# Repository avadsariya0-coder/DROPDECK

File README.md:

# DROPDECK
A Macropad with dual mode.
___________________________________________________________________________________________________________________________________________________________________________

## Overview

Dropdeck is compact custom built macropad with 5 machanical switches,1 infinite rotary encoder , 1 potentiometer and seed studio XIAO RP2040.128X32 pixels display
Dropdeck has 2 modes chill mode for the normal usage like desktop productivity and the Beast mode for the AAA title gaming.
___________________________________________________________________________________________________________________________________________________________________________

## Inspiration

The inspiration for the Dropdeck came from challenge faced by me during the gaming and normal usage to use shortcuts.
The Dropdeck fixes that problems as in chill mode it will help in using shortcuts easily for opening/closing tab,screenshot and in Beastmode or quick game interactions like healing , loadout etc
It is not built to replace the keyboard its built to make life easier while gaming and productive task.
___________________________________________________________________________________________________________________________________________________________________________

## Features

• dual modes

• analog volume mixer

• quick actions in game

•  Volume increase and decrease
_________________________________________________________________________________________________________________________________________________________________________

## Gallery

_________________________________________________________________________________________________________________________________________________________________________

## Hardware Stack

• 5X MX cherry mechanical switches

• 1X infinite rotary encoder

• 1X Potentiomrter

• 1X 128X32 pixels Display

• 1X Seed stiudio XIAO RP2040
_________________________________________________________________________________________________________________________________________________________________________

## Bill Of Material

[BOM DROPDECK.csv](https://github.com/user-attachments/files/29165464/BOM.DROPDECK.csv)
_________________________________________________________________________________________________________________________________________________________________________

## Zine 

_________________________________________________________________________________________________________________________________________________________________________

## PCB Design

The PCB used is custom designed using kicad. It includes MX cherry switches,display,potentiometer,rotary encoder,XIAO RP2040

## Features

• Custom Design

• Compact Design

• Mechanical switches

• Potentiometer

• rotary encoder
_________________________________________________________________________________________________________________________________________________________________________

## PCB

_________________________________________________________________________________________________________________________________________________________________________

## Schematic

_________________________________________________________________________________________________________________________________________________________________________

## Enclosure

The enclosure is designed using Fusion 360.

## Features

• USB-C opening

• Accesible switches,potentiometer,rotary encoder

• Display opening
_________________________________________________________________________________________________________________________________________________________________________

## Assembly Guide

• Solder Xiao RP2040 to the PCB

• Solder switches make sure that it exactly passes through the hole

• Solder Display,potentiometer,Rotary encoder

• Now fix PCB to the bottom enclosure with the help of the M2.5 Screws

• Fix the top case with the help of the Screws
_________________________________________________________________________________________________________________________________________________________________________

## How to use
•  connect it with any USB-C cable

•  The Display shows the mode

• Use switch 5 to change between modes

### chill mode

• switch 1 : Open Tab

• switch 2 : Close Tab

• switch 3 : Screenshot

• switch 4 : Show desktop

• Potentiometer : Analog volume mixer

• Rotary Encoder : Changing volume

### Beast mode

• switch 1 : Heal 

• switch 2 : Tactital ability

• switch 3 : Reload

• switch 4 : Loot/interact

• Potentiometer : Analog volume mixer

• Rotary Encoder : Change inventory
_________________________________________________________________________________________________________________________________________________________________________

## Contributing

Contributions,suggestions, and feedback are welcome

If you'd like to improve DROPDECK
1. Fork or clone the repository
   
(https://github.com/avadsariya0-coder/DROPDECK)

4. Create your Feature branch

5. Commit your changes

6. Open a pull request.

_________________________________________________________________________________________________________________________________________________________________________

## Creator

# Arman Vadsariya

17•India•Fallout

_________________________________________________________________________________________________________________________________________________________________________

## License

This project is licensed under MIT License.

_________________________________________________________________________________________________________________________________________________________________________

# DROPDECK

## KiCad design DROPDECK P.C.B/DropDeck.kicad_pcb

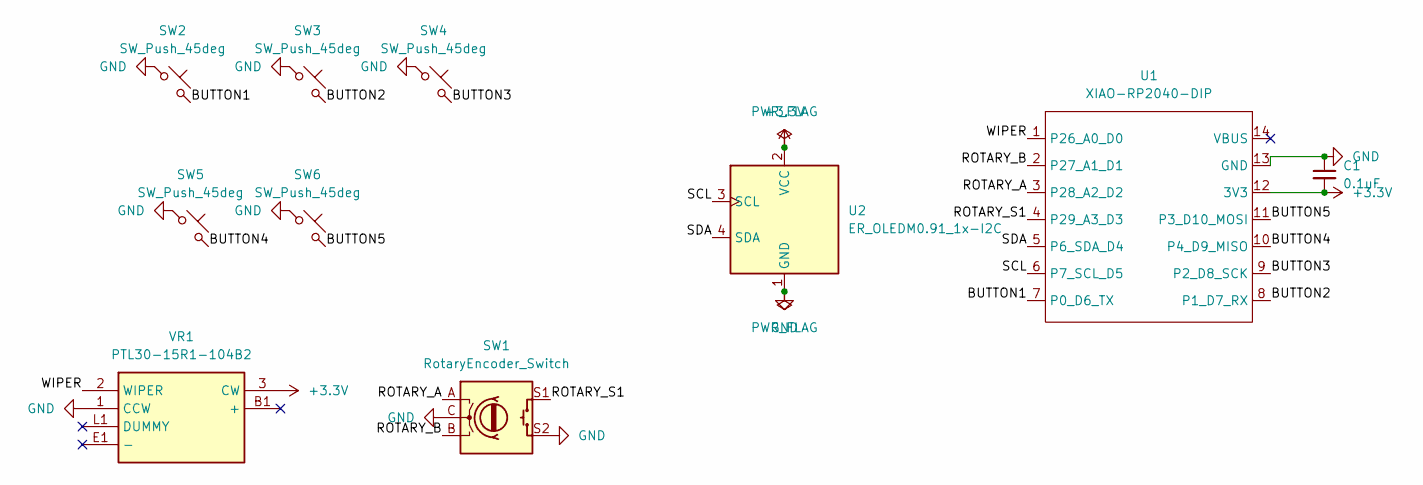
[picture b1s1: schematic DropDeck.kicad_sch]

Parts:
C1: 0.1uF; C_0805_2012Metric
SW1: RotaryEncoder_Switch; RotaryEncoder_Bourns_Vertical_PEC12R-3x17F-Sxxxx
SW2, SW3, SW4, SW5, SW6: SW_Push_45deg; SW_Cherry_MX_1.00u_PCB
U1: XIAO-RP2040-DIP
U2: ER_OLEDM0.91_1x-I2C
VR1: PTL30-15R1-104B2; PTL3015R1104B2; Manufacturer_Part_Number PTL30-15R1-104B2

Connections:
+3.3V: C1.2, U1.12 (3V3), U2.2 (VCC), VR1.3 (CW)
/BUTTON1: SW2.2, U1.7 (P0_D6_TX)
/BUTTON2: SW3.2, U1.8 (P1_D7_RX)
/BUTTON3: SW4.2, U1.9 (P2_D8_SCK)
/BUTTON4: SW5.2, U1.10 (P4_D9_MISO)
/BUTTON5: SW6.2, U1.11 (P3_D10_MOSI)
/ROTARY_A: SW1.A, U1.3 (P28_A2_D2)
/ROTARY_B: SW1.B, U1.2 (P27_A1_D1)
/ROTARY_S1: SW1.S1, U1.4 (P29_A3_D3)
/SCL: U1.6 (P7_SCL_D5), U2.3 (SCL)
/SDA: U1.5 (P6_SDA_D4), U2.4 (SDA)
/WIPER: U1.1 (P26_A0_D0), VR1.2 (WIPER)
GND: C1.1, SW1.C, SW1.S2, SW2.1, SW3.1, SW4.1, SW5.1, SW6.1, U1.13 (GND), U2.1 (GND), VR1.1 (CCW)

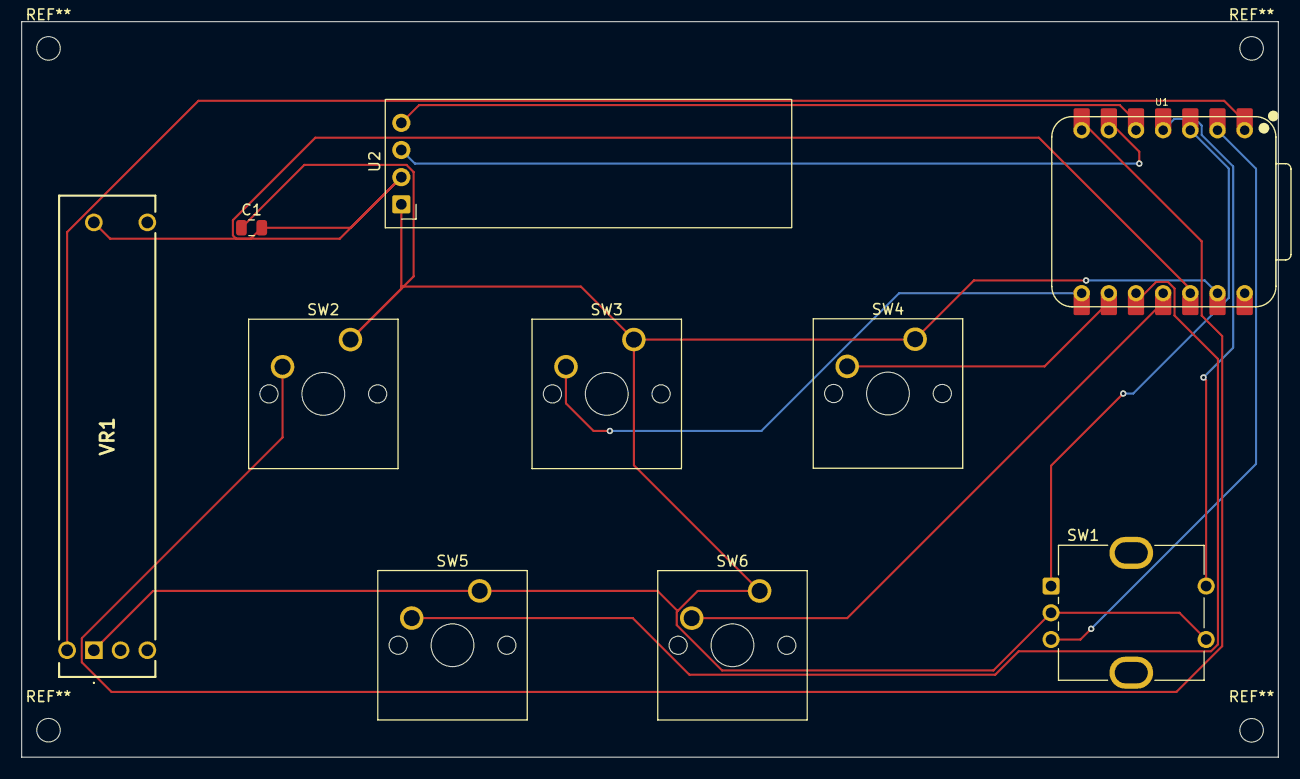
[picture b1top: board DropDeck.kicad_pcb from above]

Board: 2 copper layers, 117.5 x 68.8 mm, 10 parts (0 on the bottom side), 13 nets.
